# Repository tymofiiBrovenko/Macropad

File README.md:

# LaTeX Macropad (RP2040)

This is a custom 15-key macropad with a rotary encoder, built specifically to optimize and speed up writing math formulas in LaTeX. It is powered by a Seeeduino XIAO RP2040 and runs on custom QMK firmware. 

I designed this project to improve my workflow when typing complex equations, combining a standard numpad with powerful, auto-navigating LaTeX macros.

## Features:

- **15 Cherry MX-style keys** in a 4x4 ortholinear matrix.
- **1 Rotary Encoder** (EC11) with a push-button switch.
- **Seeeduino XIAO RP2040** microcontroller for plenty of processing power and memory.
- **Custom QMK Firmware** tailored for LaTeX.
- **Smart Cursor Navigation:** Macros automatically move the cursor inside the brackets after typing a command (e.g., pasting `\frac{}{}` automatically steps back into the first set of brackets).

## CAD Model

The enclosure was custom-designed for this build to hold the PCB, the switches, and the XIAO RP2040 securely. 

## PCB & Schematic

The PCB was designed to accommodate the 4x4 matrix layout. It uses standard 1N4148 diodes configured in `COL2ROW` direction.

*Note: The schematic might show SAMD21 pinouts (D0, D1, etc.) from the footprint library, but the hardware uses the XIAO RP2040, so the firmware is mapped to the exact RP2040 hardware pins (GP26, GP6, etc.).*

## Firmware Overview

This macropad uses QMK Firmware to handle the matrix, the encoder, and the complex macros.

**Keymap Layers:**
- **Base Layer (`_NUMPAD`):** Acts as a standard numpad for quick number entry. Includes a dedicated layer-modifier key.
- **LaTeX Layer (`_LATEX`):** Accessed by holding the modifier key. Contains 14 of the most used LaTeX commands (`\frac{}{}`, `\sqrt{}`, `\sum_{}^{}`, `\int_{}^{}`, etc.).

**Rotary Encoder:**
- **Rotate Left/Right:** Moves the text cursor left and right (perfect for navigating inside long equations).
- **Press:** Acts as a Left Mouse Button click.

## BOM

Here is everything you need to build this macropad:

- 1x Seeeduino XIAO RP2040
- 15x Cherry MX-style Switches
- 15x Keycaps
- 1x Rotary Encoder
- 1x Encoder Knob
- 15x 1N4148 Diodes
- Custom printed PCB & 3D Printed Case(2 parts)
- Screws (M2.5x10mm SHCS) and heat-set inserts (M2.5x4x3.5)

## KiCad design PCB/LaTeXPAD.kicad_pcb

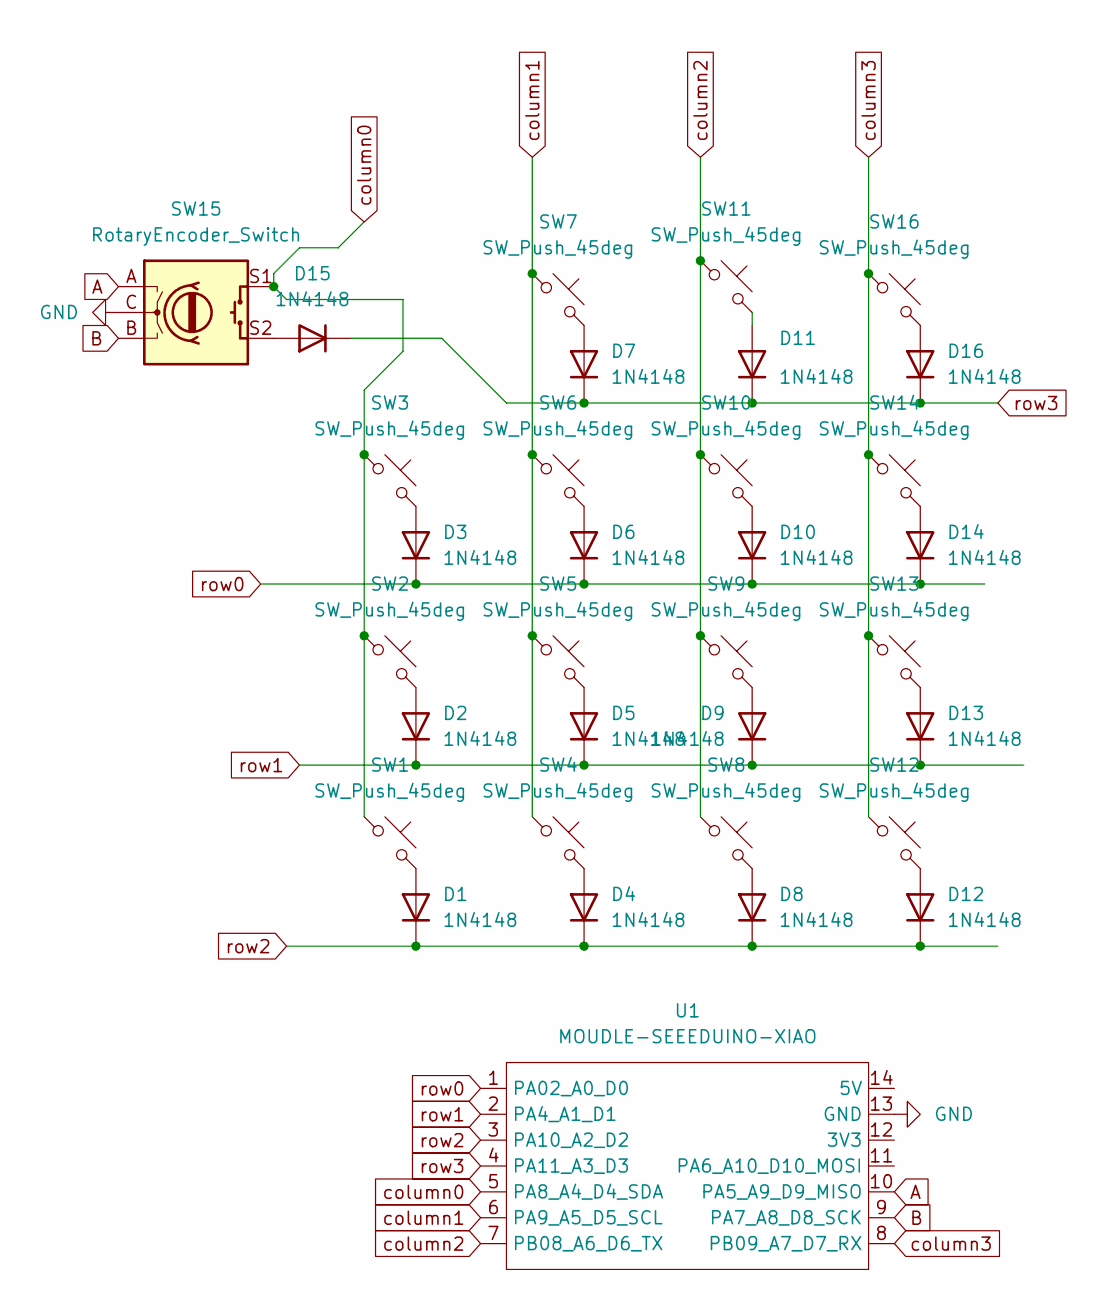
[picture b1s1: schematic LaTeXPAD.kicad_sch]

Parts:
D1, D2, D3, D4, D5, D6, D7, D8, D9, D10, D11, D12, D13, D14, D15, D16: 1N4148; D_DO-35_SOD27_P7.62mm_Horizontal
SW1, SW2, SW3, SW4, SW5, SW6, SW7, SW8, SW9, SW10, SW11, SW12, SW13, SW14, SW16: SW_Push_45deg; SW_Cherry_MX_1.00u_PCB
SW15: RotaryEncoder_Switch; RotaryEncoder_Alps_EC11E-Switch_Vertical_H20mm
U1: MOUDLE-SEEEDUINO-XIAO; XIAO-Generic-Hybrid-14P-2.54-21X17.8MM

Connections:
A: SW15.A, U1.10 (PA5_A9_D9_MISO)
B: SW15.B, U1.9 (PA7_A8_D8_SCK)
GND: SW15.C, U1.13 (GND)
unnamed: D1.2 (A), SW1.2
unnamed: D2.2 (A), SW2.2
unnamed: D3.2 (A), SW3.2
unnamed: D4.2 (A), SW4.2
unnamed: D5.2 (A), SW5.2
unnamed: D6.2 (A), SW6.2
unnamed: D7.2 (A), SW7.2
unnamed: D8.2 (A), SW8.2
unnamed: D9.2 (A), SW9.2
unnamed: D10.2 (A), SW10.2
unnamed: D11.2 (A), SW11.2
unnamed: D12.2 (A), SW12.2
unnamed: D13.2 (A), SW13.2
unnamed: D14.2 (A), SW14.2
unnamed: D15.2 (A), SW15.S2
unnamed: D16.2 (A), SW16.2
column0: SW1.1, SW2.1, SW3.1, SW15.S1, U1.5 (PA8_A4_D4_SDA)
column1: SW4.1, SW5.1, SW6.1, SW7.1, U1.6 (PA9_A5_D5_SCL)
column2: SW8.1, SW9.1, SW10.1, SW11.1, U1.7 (PB08_A6_D6_TX)
column3: SW12.1, SW13.1, SW14.1, SW16.1, U1.8 (PB09_A7_D7_RX)
row0: D3.1 (K), D6.1 (K), D10.1 (K), D14.1 (K), U1.1 (PA02_A0_D0)
row1: D2.1 (K), D5.1 (K), D9.1 (K), D13.1 (K), U1.2 (PA4_A1_D1)
row2: D1.1 (K), D4.1 (K), D8.1 (K), D12.1 (K), U1.3 (PA10_A2_D2)
row3: D7.1 (K), D11.1 (K), D15.1 (K), D16.1 (K), U1.4 (PA11_A3_D3)

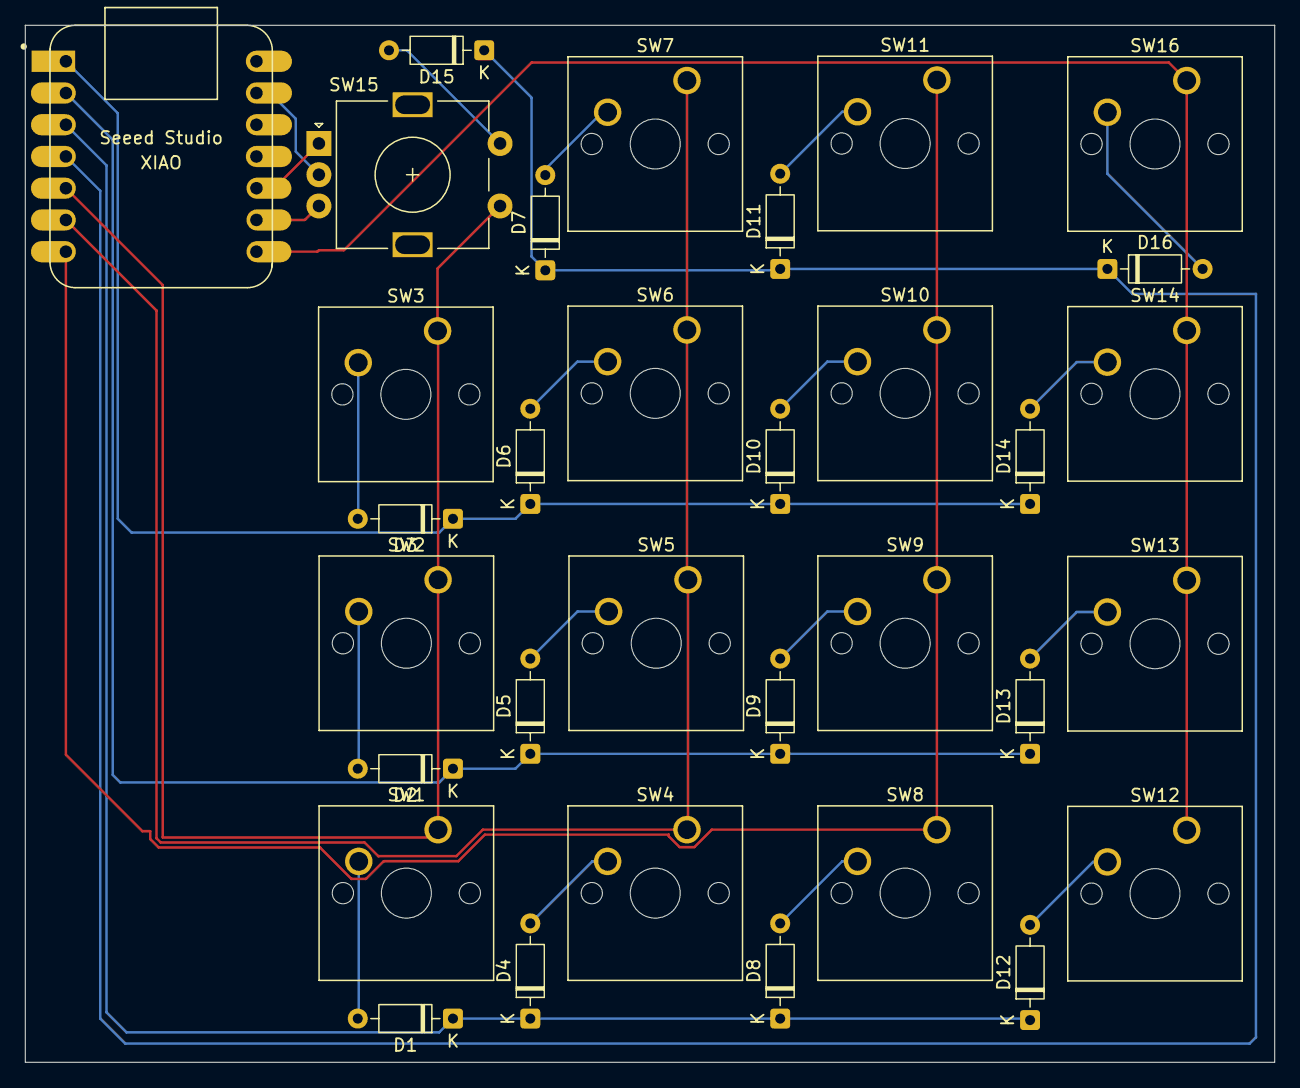
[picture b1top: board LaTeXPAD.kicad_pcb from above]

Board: 2 copper layers, 100.0 x 83.0 mm, 33 parts (0 on the bottom side), 27 nets.

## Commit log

2026-03-24 Enhance README with project details and specifications
    Expanded README to include detailed project description, features, CAD model, PCB design, firmware overview, and BOM.
2026-03-26 Rename gerbers.zip to gebers.zip
2026-06-14 Fix CAD software name in Readme2.md
2026-06-14 Replace placeholder image with actual image link
    Updated the image link in the README file.
2026-06-14 Add Logik section with image to Readme2.md
    Added a section for Logik with an image in Readme2.md.
2026-06-14 Rename Readme2.md to README.md
2026-06-14 Remove placeholder for additional components
    Removed placeholder for additional components from the README.
